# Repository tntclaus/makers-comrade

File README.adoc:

= Komrade of Maker (universal CNC platform)

[.right]
.First prototype, build volume (mm) 580x580x580
image::docs/img/photo_km-5.8.jpeg["First prototype",360]

This design is universal platform, that uses where available affordable parts, primarily from Reprap project, 8 bit realtime controllers, RPi 3/4 and Klipper.

Primary characteristics by application:

* 3D printing:
** Enclosed chamber passively heated up to 80ºC;
** Filament motion control;
** Auto bed levelling with Piezo Sensor and triple z axis;
** X/Y Linear speeds up to 200 mm/s (or greater with proper voltage/servos);
** Ceramic build surface.
* Milling with 585 series motors:
** Soft materials, e.g.: sheet plastics, plywood, aluminium (not tested);
** PCB prototyping.
* Laser cutting/engraving.
* Electrochemical machining.

== BOM
=== Base vitamins

.Base components common for all models
[cols="5,1,1,1",options="header",]
|===
|Part |Amount |Aliexpress |Amazon
|RAMPS 1.6+ |1 | - |-
|Arduino Mega |1 | - | -
|HDMI LCD 7" |1 | - | -
|RPi 3/4 |1 | - | -
|RPi Camera |1 | - | -
|RPi Motor Shield |1 | - | -
|Nema 17 steppers |5 | - | -
|X/Y axis MKS-Servo 42C |2 | - | -
|TMC 2209 |4 | - | -
|D16T parts set for universal X caret |1 | - | -
|V Slot Wheels|23 | - | -
|Steel parts for Z axis mount |1 | - | -
|Z axis axial bearing | 3 | - | -
|Z axis flexible coupler 5*8 |3 | - | -
|steel ball ø8mm |3 | - | -
|===

.Orbiter Extruder 3D Printer Toolhead
[cols="5,1,1,1",options="header",]
|===
|Part |Amount |Aliexpress |Amazon
|Extruder Orbiter with LDO stepper |1 | - | -
|Filament motion sensor |1 | - | -
|Crazy NF hotend | 1 | - | -
|===

=== Model KМ—3

Build Volume (mm): 300x300x300

[cols=",,,",options="header",]
|===
|Part |Amount |Aliexpress |Amazon
|  leadscrew  350 mm|  3  |  - | -
|  2020 VSlot extrusion 450 mm | 12 | - | -
|  2020 VSlot extrusion 850 mm | 4 | - | -
|  2040 VSlot extrusion 450 mm | 2 | - | -
|  GT6 Gates Belt (m) |  3  |  - | -
|===

=== Model KМ—6

Build Volume (mm): 600x600x600

== Dependencies

https://github.com/nophead/NopSCADlib
https://github.com/openscad/scad-utils
https://github.com/oysteinkrog/thing_libutils
https://github.com/Obijuan/obiscad

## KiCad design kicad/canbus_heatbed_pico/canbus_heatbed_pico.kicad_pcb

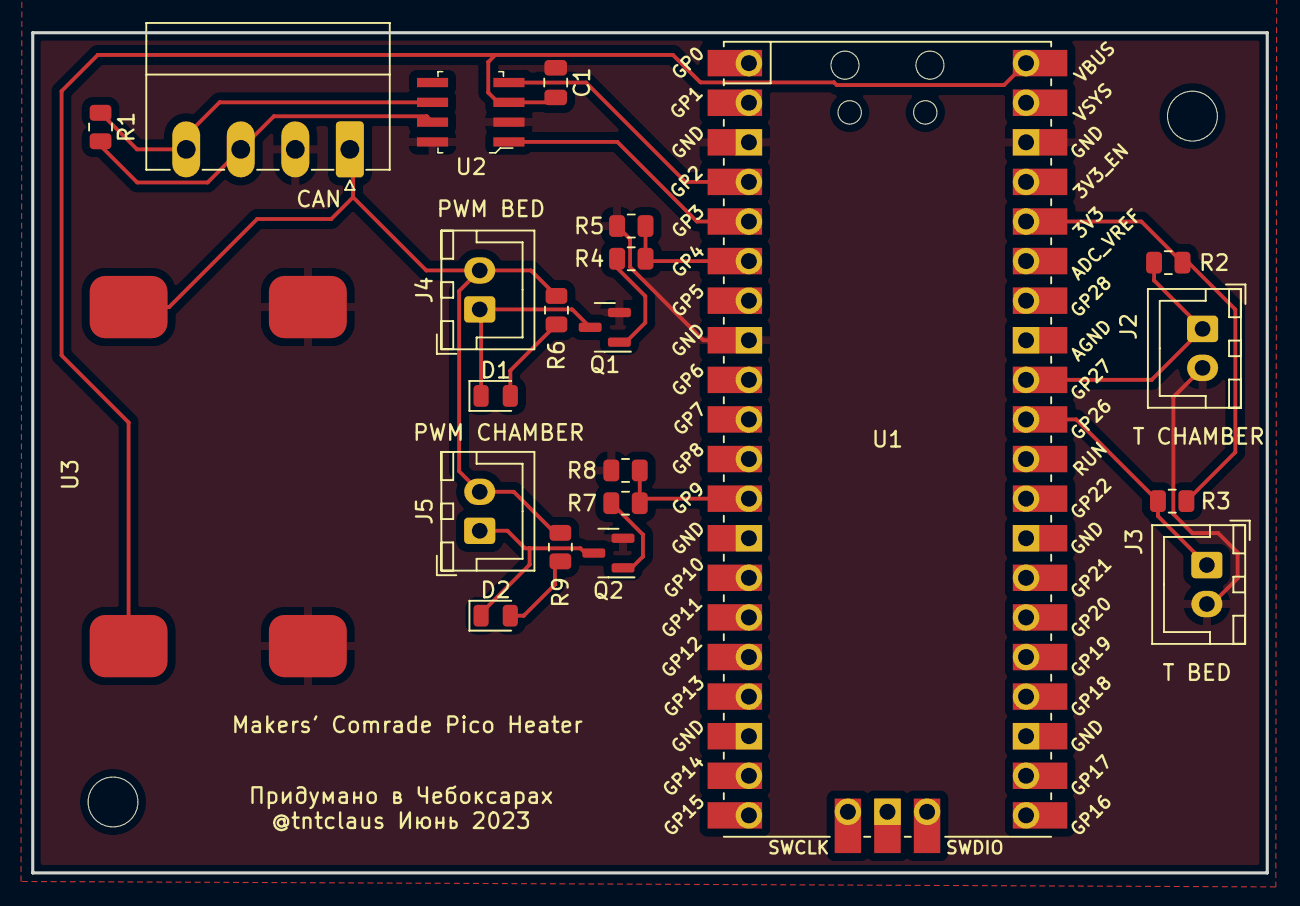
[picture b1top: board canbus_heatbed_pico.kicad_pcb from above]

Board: 2 copper layers, 79.2 x 53.9 mm, 24 parts (0 on the bottom side), 18 nets.

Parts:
C1: 0.1µF; C_0805_2012Metric
D1, D2: XL-2012UGC; LED_0805_2012Metric
H1, H2: MountingHole; MountingHole_3.2mm_M3_DIN965
J1: CAN; PhoenixContact_MC_1,5_4-G-3.5_1x04_P3.50mm_Horizontal
J2: T CHAMBER; JST_XH_B2B-XH-A_1x02_P2.50mm_Vertical
J3: T BED; JST_XH_B2B-XH-A_1x02_P2.50mm_Vertical
J4: PWM BED; JST_XH_B2B-XH-A_1x02_P2.50mm_Vertical
J5: PWM CHAMBER; JST_XH_B2B-XH-A_1x02_P2.50mm_Vertical
Q1, Q2: 2N7002K; SOT-23
R1: 120; R_0805_2012Metric
R2, R3, R5, R6, R8, R9: 4.7k; R_0805_2012Metric
R4, R7: 200; R_0805_2012Metric
U1: Pico; RPi_Pico_SMD_TH
U2: SN65HVD230DR; SOIC-8_W3.9mm
U3: MP1584EN 5V; MP1584EN

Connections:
+3V3: R2.1, R3.1, U1.36 (3V3)
+5V: C1.2, U1.40 (VBUS), U2.3 (VCC), U3.1 (5V)
+24V: J1.1, J4.2, J5.2, R6.2, R9.2, U3.3 (Vin+)
/CAN_RX: U1.4 (GPIO2), U2.4 (R)
/CAN_TX: U1.5 (GPIO3), U2.1 (D)
/H: J1.4, R1.1, U2.6 (CANL)
/L: J1.3, R1.2, U2.7 (CANH)
/PWM BED: R4.1, R5.1, U1.6 (GPIO4)
/PWM CHAMBER: R7.1, R8.1, U1.12 (GPIO9)
/T BED: J3.1, R3.2, U1.31 (GPIO26_ADC0)
/T CHAMBER: J2.1, R2.2, U1.32 (GPIO27_ADC1)
GND: C1.1, J1.2, J2.2, J3.2, Q1.2 (S), Q2.2 (S), R5.2, R8.2, U1.3 (GND), U1.8 (GND), U1.38 (GND), U2.2 (GND), U2.8 (RS), U3.2 (GND), U3.4 (Vin-)
unnamed: D1.1 (K), J4.1, Q1.3 (D)
unnamed: D1.2 (A), R6.1
unnamed: D2.1 (K), J5.1, Q2.3 (D)
unnamed: D2.2 (A), R9.1
unnamed: Q1.1 (G), R4.2
unnamed: Q2.1 (G), R7.2

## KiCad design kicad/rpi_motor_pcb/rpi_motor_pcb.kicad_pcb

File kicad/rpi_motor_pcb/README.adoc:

= Makers' Comrade CNC HAT

image::docs/pcb_3d.png[]

6-осевой ЧПУ шилд для Raspberry Pi 3B, 3B+, 4.

Возможности:

* Одновременное управление 6 драйверами шаговых двигателей:
** Поддерживаемые драйвера:
*** TMC2209, TMC2208 — режим UART с указанием адреса через перемычки MS1/MS2;
*** DRV8820, A4988 — обычный режим с конфигурацией через перемычки MS1,MS2,MS3;
* Любые другие драйвера, поддерживающие DIR/STEP.
* Суммарная пиковая производительность всех двигателей 1018 тыс. шагов/секунду (Klipper с патчем, Linux CNC не тестировался, но вероятно будет результат того же порядка).
* Поддержка концевиков для осей X, Y, Z, A, B, C как стандартного типа, так и DIAG выходов для без сенсорной парковки драйвера TMC2209.
* Поддержка дополнительного концевика (например, для датчика наличия/движения филамента 3д принтера).
* CANBUS host на базе MCP2515 и трансивера SN65HVD230:
** Даёт возможность гибкого дополнения станка периферией:
*** С контроллером экструдера https://github.com/makerbase-mks/MKS-THR36-THR42-UTC[MKS THR36] можно использовать как 3d принтер (не помешает canbus контроллер нагревательного стола/камеры).
*** С canbus контроллером шпинделя можно использовать как ЧПУ фрезер.
*** ...и т.д.
* Управление PWM нагрузкой с током до 1А (вентилятор обдува, маломощный двигатель).
* Поддерживаемые системы: Linux CNC, Klipper.

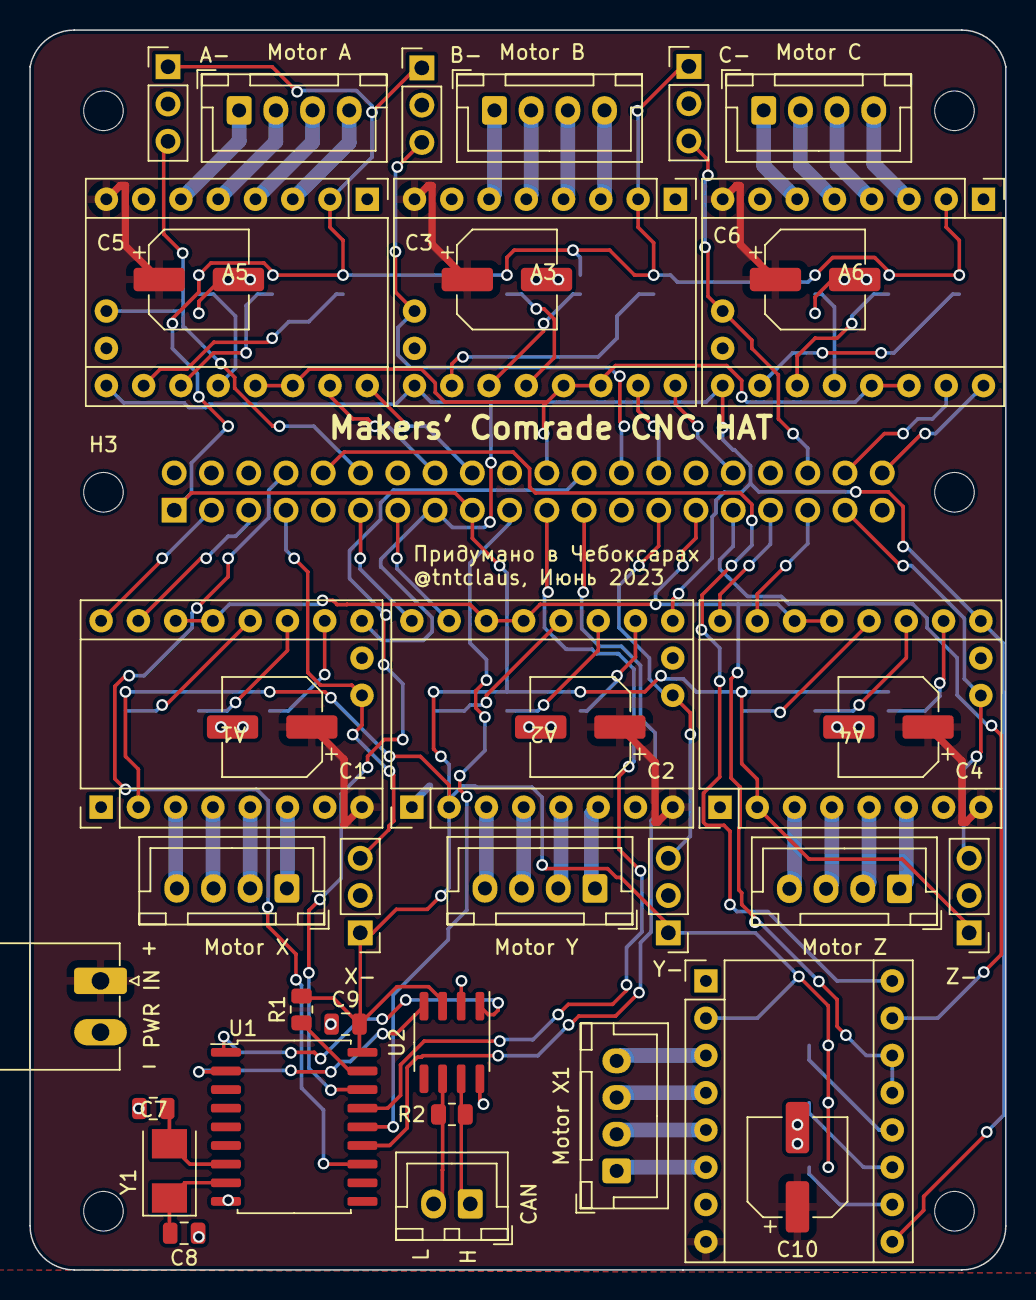
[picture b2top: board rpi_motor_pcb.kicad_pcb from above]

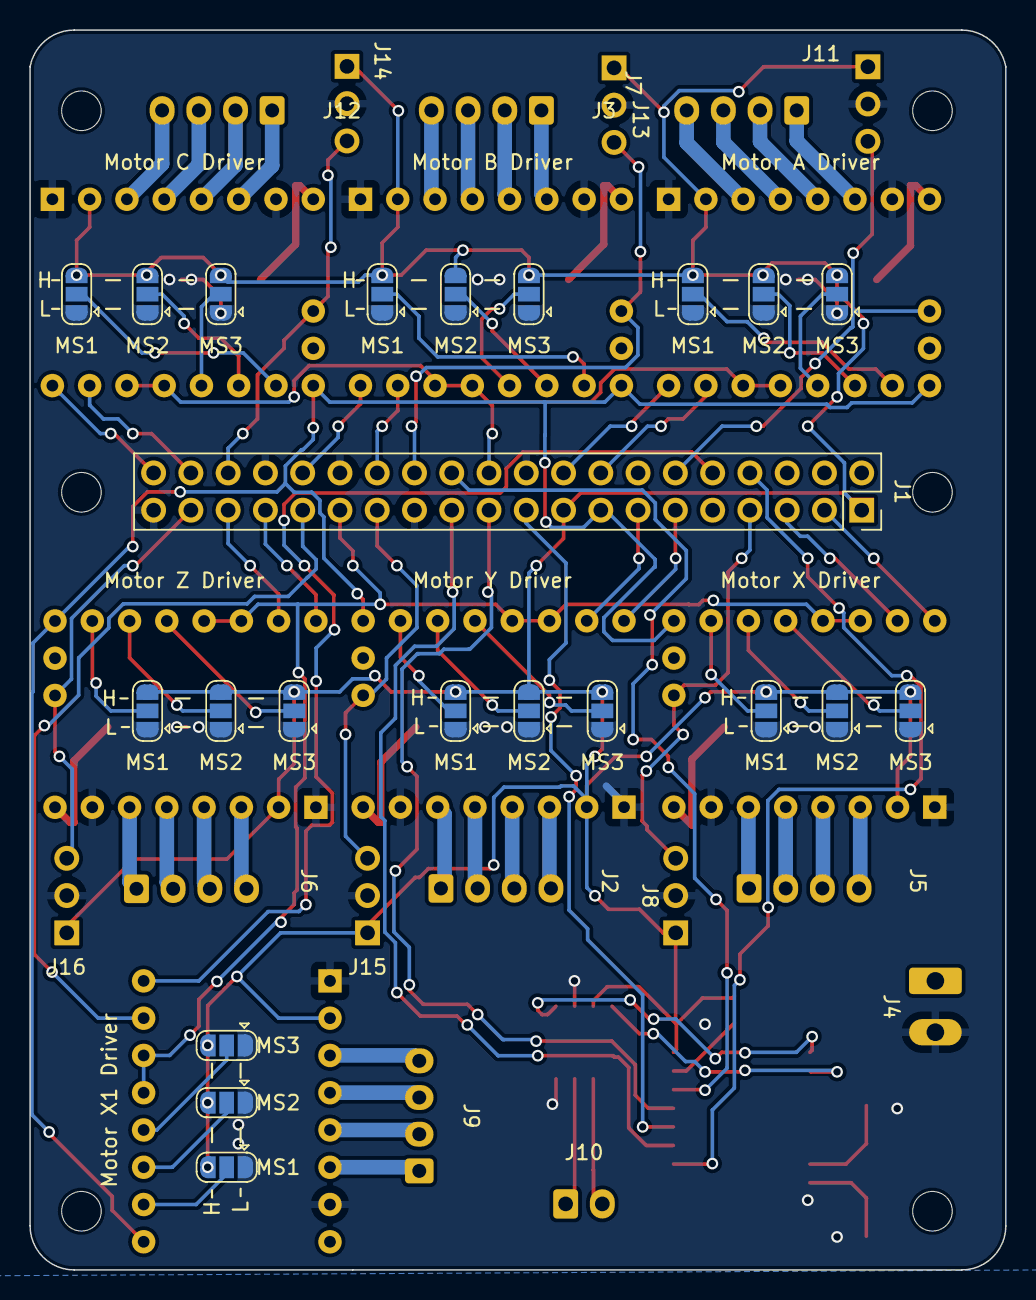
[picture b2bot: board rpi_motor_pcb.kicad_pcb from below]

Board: 2 copper layers, 66.5 x 84.5 mm, 65 parts (22 on the bottom side), 87 nets.

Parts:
A1: Motor X Driver; TMC220X
A2: Motor Y Driver; TMC220X
A3: Motor B Driver; TMC220X
A4: Motor Z Driver; TMC220X
A5: Motor A Driver; TMC220X
A6: Motor C Driver; TMC220X
A7: Motor X1 Driver; TMC2208
C1, C2, C3, C4, C5, C6, C10: 100µF 50V; CP_Elec_6.3x7.7
C7, C8: 22pF; C_0805_2012Metric
C9: 0.1µF; C_0805_2012Metric
H1, H2, H3, H4, H5, H6: MountingHole; MountingHole_2.7mm_M2.5_ISO14580
J1: Raspberry_Pi_2_3; PinSocket_2x20_P2.54mm_Vertical
J2: Motor Y; JST_XH_B4B-XH-A_1x04_P2.50mm_Vertical
J3: Motor B; JST_XH_B4B-XH-A_1x04_P2.50mm_Vertical
J4: PWR IN; PhoenixContact_MC_1,5_2-G-3.5_1x02_P3.50mm_Horizontal
J5: Motor X; JST_XH_B4B-XH-A_1x04_P2.50mm_Vertical
J6: Motor Z; JST_XH_B4B-XH-A_1x04_P2.50mm_Vertical
J7: Motor A; JST_XH_B4B-XH-A_1x04_P2.50mm_Vertical
J8: X-; PinHeader_1x03_P2.54mm_Vertical
J9: Motor X1; JST_XH_B4B-XH-A_1x04_P2.50mm_Vertical
J10: CAN; JST_XH_B2B-XH-A_1x02_P2.50mm_Vertical
J11: A-; PinHeader_1x03_P2.54mm_Vertical
J12: Motor C; JST_XH_B4B-XH-A_1x04_P2.50mm_Vertical
J13: B-; PinHeader_1x03_P2.54mm_Vertical
J14: C-; PinHeader_1x03_P2.54mm_Vertical
J15: Y-; PinHeader_1x03_P2.54mm_Vertical
J16: Z-; PinHeader_1x03_P2.54mm_Vertical
JP1, JP4, JP7, JP10, JP13, JP16, JP19: MS3; SolderJumper-3_P1.3mm_Open_RoundedPad1.0x1.5mm
JP2, JP5, JP8, JP11, JP14, JP17, JP20: MS2; SolderJumper-3_P1.3mm_Open_RoundedPad1.0x1.5mm
JP3, JP6, JP9, JP12, JP15, JP18, JP21: MS1; SolderJumper-3_P1.3mm_Open_RoundedPad1.0x1.5mm
R1: 10k; R_0805_2012Metric
R2: 120; R_0805_2012Metric
U1: MCP2515-xSO; SOIC-18W_7.5x11.6mm_P1.27mm
U2: SN65HVD230; SOIC-8_3.9x4.9mm_P1.27mm
Y1: Crystal; Crystal_SMD_5032-2Pin_5.0x3.2mm

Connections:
+3V3: A1.2 (VDD), A2.2 (VDD), A3.2 (VDD), A4.2 (VDD), A5.2 (VDD), A6.2 (VDD), A7.2 (VDD), C9.2, J1.1 (3V3), J1.17 (3V3), J8.1, J11.1, J13.1, J14.1, J15.1, J16.1, JP1.3 (B), JP2.3 (B), JP3.3 (B), JP4.3 (B), JP5.3 (B), JP6.3 (B), JP7.3 (B), JP8.3 (B), JP9.3 (B), JP10.3 (B), JP11.3 (B), JP12.3 (B), JP13.3 (B), JP14.3 (B), JP15.3 (B), JP16.3 (B), JP17.3 (B), JP18.3 (B), JP19.3 (B), JP20.3 (B), JP21.3 (B), R1.2, U1.18 (VDD), U2.3 (VCC)
/CAN/H: J10.1, R2.1, U2.7 (CANH)
/CAN/L: J10.2, R2.2, U2.6 (CANL)
/CAN/RX: U1.2 (RXCAN), U2.4 (R)
/CAN/TX: U1.1 (TXCAN), U2.1 (D)
/CAN_CS: J1.24 (~CE0/GPIO8), U1.16 (~CS)
/CAN_INT: J1.8 (GPIO14/TXD), U1.12 (~INT)
/CAN_MISO: J1.21 (MISO0/GPIO9), U1.15 (SO)
/CAN_MOSI: J1.19 (MOSI0/GPIO10), U1.14 (SI)
/CAN_SCK: J1.23 (SCLK0/GPIO11), U1.13 (SCK)
/MA DIAG: A5.18 (DIAG), J1.12 (GPIO18/PWM0), J11.3
/MA DIR: A5.16 (DIR), J1.18 (GPIO24)
/MA STEP: A5.15 (STEP), J1.16 (GPIO23)
/MB DIAG: A3.18 (DIAG), J1.26 (~CE1/GPIO7), J13.3
/MB DIR: A3.16 (DIR), J1.32 (PWM0/GPIO12)
/MB STEP: A3.15 (STEP), J1.28 (ID_SC/GPIO1)
/MC DIAG: A6.18 (DIAG), J1.36 (GPIO16), J14.3
/MC DIR: A6.16 (DIR), J1.40 (GPIO21/SCLK1)
/MC STEP: A6.15 (STEP), J1.38 (GPIO20/MOSI1)
/MX1 DIR: A7.16 (DIR), J1.10 (GPIO15/RXD)
/MX1 STEP: A7.15 (STEP), J1.31 (GCLK2/GPIO6)
/MX DIAG: A1.18 (DIAG), J1.7 (GCLK0/GPIO4), J8.3
/MX DIR: A1.16 (DIR), J1.3 (SDA/GPIO2)
/MX STEP: A1.15 (STEP), J1.5 (SCL/GPIO3)
/MY DIAG: A2.18 (DIAG), J1.27 (ID_SD/GPIO0), J15.3
/MY DIR: A2.16 (DIR), J1.11 (GPIO17)
/MY STEP: A2.15 (STEP), J1.13 (GPIO27)
/MZ DIAG: A4.18 (DIAG), J1.37 (GPIO26), J16.3
/MZ DIR: A4.16 (DIR), J1.33 (PWM1/GPIO13)
/MZ STEP: A4.15 (STEP), J1.35 (GPIO19/MISO1)
/Motor A/1A: A5.4 (1A), J7.3
/Motor A/1B: A5.3 (1B), J7.4
/Motor A/2A: A5.5 (2A), J7.2
/Motor A/2B: A5.6 (2B), J7.1
/Motor A/MS1: A5.10 (MS1), JP15.2 (C)
/Motor A/MS2: A5.11 (MS2), JP14.2 (C)
/Motor A/MS3: A5.12 (NC/TX), JP13.2 (C)
/Motor B/1A: A3.4 (1A), J3.3
/Motor B/1B: A3.3 (1B), J3.4
/Motor B/2A: A3.5 (2A), J3.2
/Motor B/2B: A3.6 (2B), J3.1
/Motor B/MS1: A3.10 (MS1), JP9.2 (C)
/Motor B/MS2: A3.11 (MS2), JP8.2 (C)
/Motor B/MS3: A3.12 (NC/TX), JP7.2 (C)
/Motor C/1A: A6.4 (1A), J12.3
/Motor C/1B: A6.3 (1B), J12.4
/Motor C/2A: A6.5 (2A), J12.2
/Motor C/2B: A6.6 (2B), J12.1
/Motor C/MS1: A6.10 (MS1), JP18.2 (C)
/Motor C/MS2: A6.11 (MS2), JP17.2 (C)
/Motor C/MS3: A6.12 (NC/TX), JP16.2 (C)
/Motor X1/1A: A7.4 (1A), J9.3
/Motor X1/1B: A7.3 (1B), J9.4
/Motor X1/2A: A7.5 (2A), J9.2
/Motor X1/2B: A7.6 (2B), J9.1
/Motor X1/MS1: A7.10 (MS1), JP21.2 (C)
/Motor X1/MS2: A7.11 (MS2), JP20.2 (C)
/Motor X1/MS3: A7.12 (NC/TX), JP19.2 (C)
/Motor X/1A: A1.4 (1A), J5.3
/Motor X/1B: A1.3 (1B), J5.4
/Motor X/2A: A1.5 (2A), J5.2
/Motor X/2B: A1.6 (2B), J5.1
/Motor X/MS1: A1.10 (MS1), JP3.2 (C)
/Motor X/MS2: A1.11 (MS2), JP2.2 (C)
/Motor X/MS3: A1.12 (NC/TX), JP1.2 (C)
/Motor Y/1A: A2.4 (1A), J2.3
/Motor Y/1B: A2.3 (1B), J2.4
/Motor Y/2A: A2.5 (2A), J2.2
/Motor Y/2B: A2.6 (2B), J2.1
/Motor Y/MS1: A2.10 (MS1), JP6.2 (C)
/Motor Y/MS2: A2.11 (MS2), JP5.2 (C)
/Motor Y/MS3: A2.12 (NC/TX), JP4.2 (C)
/Motor Z/1A: A4.4 (1A), J6.3
/Motor Z/1B: A4.3 (1B), J6.4
/Motor Z/2A: A4.5 (2A), J6.2
/Motor Z/2B: A4.6 (2B), J6.1
/Motor Z/MS1: A4.10 (MS1), JP12.2 (C)
/Motor Z/MS2: A4.11 (MS2), JP11.2 (C)
/Motor Z/MS3: A4.12 (NC/TX), JP10.2 (C)
/UART_A: A3.13 (PDN/RX), A3.14 (NC/CLK), A5.13 (PDN/RX), A5.14 (NC/CLK), A6.13 (PDN/RX), A6.14 (NC/CLK), J1.22 (GPIO25)
/UART_X: A1.13 (PDN/RX), A1.14 (NC/CLK), A2.13 (PDN/RX), A2.14 (NC/CLK), A4.13 (PDN/RX), A4.14 (NC/CLK), A7.13 (PDN/RX), A7.14 (NC/CLK), J1.29 (GCLK1/GPIO5)
GND: A1.1 (GND), A1.7 (GND), A2.1 (GND), A2.7 (GND), A3.1 (GND), A3.7 (GND), A4.1 (GND), A4.7 (GND), A5.1 (GND), A5.7 (GND), A6.1 (GND), A6.7 (GND), A7.1 (GND), A7.7 (GND), C1.2, C2.2, C3.2, C4.2, C5.2, C6.2, C7.1, C8.1, C9.1, C10.2, J1.20 (GND), J1.25 (GND), J1.30 (GND), J1.34 (GND), J1.39 (GND), J4.2, J8.2, J11.2, J13.2, J14.2, J15.2, J16.2, JP1.1 (A), JP2.1 (A), JP3.1 (A), JP4.1 (A), JP5.1 (A), JP6.1 (A), JP7.1 (A), JP8.1 (A), JP9.1 (A), JP10.1 (A), JP11.1 (A), JP12.1 (A), JP13.1 (A), JP14.1 (A), JP15.1 (A), JP16.1 (A), JP17.1 (A), JP18.1 (A), JP19.1 (A), JP20.1 (A), JP21.1 (A), U1.9 (VSS), U2.2 (GND), U2.8 (Rs)
MEN: A1.9 (~ENABLE), A2.9 (~ENABLE), A3.9 (~ENABLE), A4.9 (~ENABLE), A5.9 (~ENABLE), A6.9 (~ENABLE), A7.9 (~ENABLE), J1.15 (GPIO22)
unnamed: C7.2, U1.7 (OSC2), Y1.2
unnamed: C8.2, U1.8 (OSC1), Y1.1
unnamed: R1.1, U1.17 (~RESET)
Vin: A1.8 (VMOT), A2.8 (VMOT), A3.8 (VMOT), A4.8 (VMOT), A5.8 (VMOT), A6.8 (VMOT), A7.8 (VMOT), C1.1, C2.1, C3.1, C4.1, C5.1, C6.1, C10.1, J4.1

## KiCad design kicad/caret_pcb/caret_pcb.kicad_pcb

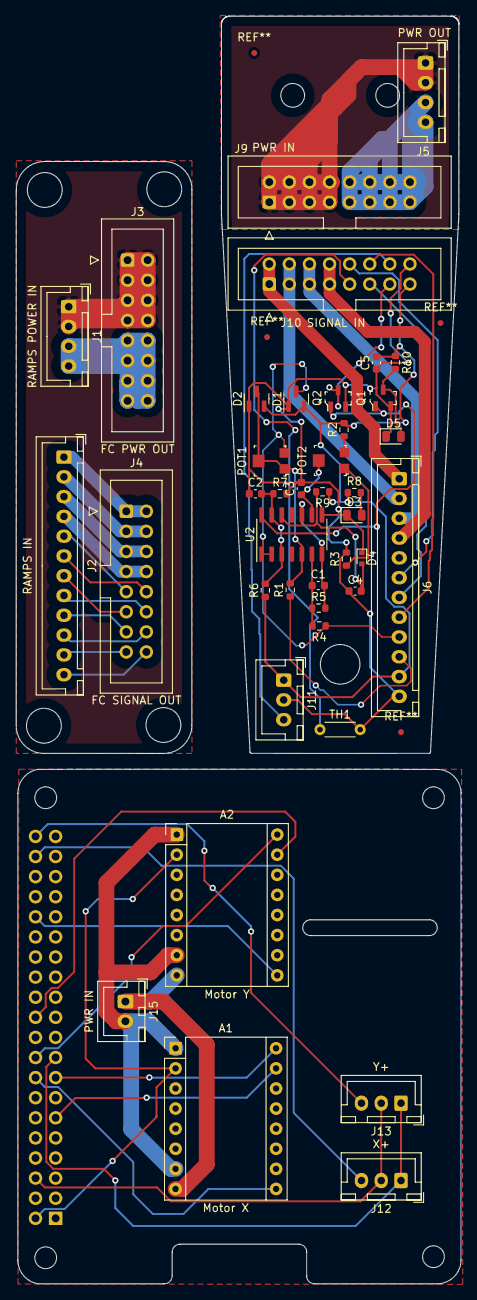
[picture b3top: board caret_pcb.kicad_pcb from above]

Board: 2 copper layers, 56.2 x 160.2 mm, 41 parts (1 on the bottom side), 55 nets.

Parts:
A1: Motor X; Pololu_Breakout-16_15.2x20.3mm
A2: Motor Y; Pololu_Breakout-16_15.2x20.3mm
C1, C2, C3: 0.1uF; C_0603_1608Metric
C4, C5: 1 uF 10 V 10%; C_0603_1608Metric
D1, D2: BAV99; SOT-23
D3: RED; D_0805_2012Metric
D4: RB751S40T1G; D_SOD-523
D5: BLUE; D_0805_2012Metric
J1: RAMPS POWER IN; JST_XH_B4B-XH-A_1x04_P2.50mm_Vertical
J2: RAMPS IN; JST_XH_B12B-XH-A_1x12_P2.50mm_Vertical
J3: FC PWR OUT; IDC-Header_2x08_P2.54mm_Vertical
J4: FC SIGNAL OUT; IDC-Header_2x08_P2.54mm_Vertical
J5: PWR OUT; JST_XH_B4B-XH-A_1x04_P2.50mm_Vertical
J6: TOOLHEAD; JST_XH_B12B-XH-A_1x12_P2.50mm_Vertical
J9: PWR IN; IDC-Header_2x08_P2.54mm_Vertical
J10: SIGNAL IN; IDC-Header_2x08_P2.54mm_Vertical
J11: Endstop Y; JST_XH_B3B-XH-A_1x03_P2.50mm_Vertical
J12: X+; JST_XH_B3B-XH-A_1x03_P2.50mm_Vertical
J13: Y+; JST_XH_B3B-XH-A_1x03_P2.50mm_Vertical
J14: Raspberry_Pi_2_3; PinSocket_2x20_P2.54mm_Vertical
J15: PWR IN; JST_XH_B2B-XH-A_1x02_P2.50mm_Vertical
POT1: TC33X-2-105; Trimpot_3.8mmx3.6mm_TC33X-2-103E
POT2: TC33X-2-104; Trimpot_3.8mmx3.6mm_TC33X-2-103E
Q1, Q2: BSS138BK; SOT-23-3
R1, R6, R7: 10k; R_0603_1608Metric
R2: 330k; R_0603_1608Metric
R3: 390k; R_0603_1608Metric
R4: 20k; R_0603_1608Metric
R5: 82k; R_0603_1608Metric
R8: 510; R_0603_1608Metric
R9: 1M; R_0603_1608Metric
R10: 1k; R_0603_1608Metric
TH1: Thermistor_NTC; R_Axial_DIN0204_L3.6mm_D1.6mm_P5.08mm_Horizontal
U2: LM324; SOIC-14_3.9x8.7mm_P1.27mm

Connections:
/Caret Adapter/1A: J6.2, J10.3, J10.4
/Caret Adapter/1B: J6.1, J10.1, J10.2
/Caret Adapter/2A: J6.3, J10.5, J10.6
/Caret Adapter/2B: J6.4, J10.7, J10.8
/Caret Adapter/5V+: C5.2, D1.2 (A), D2.2 (A), J6.11, J10.15, J11.1, R2.2, R6.1, R8.1, R9.1, R10.1
/Caret Adapter/End.Y: J10.14, J11.3
/Caret Adapter/GND: C2.1, C3.2, C4.1, C5.1, D1.1 (K), D2.1 (K), D5.1 (K), J6.12, J10.16, J11.2, Q1.2 (S), Q2.2 (S), R3.2, R7.2, TH1.2
/Caret Adapter/HE0+: J5.1, J5.2, J9.1, J9.2, J9.3, J9.4, J9.5, J9.6, J9.7, J9.8
/Caret Adapter/PWM 5V: J6.8, J10.12
/Caret Adapter/PZ+: D1.3 (K), J6.9, POT1.3 (CW), R4.1, U2.1, U2.2 (-)
/Caret Adapter/PZ-: J6.10, R1.1
/Caret Adapter/T.enc: J10.9, TH1.1
/Caret Adapter/T.ext: J6.6, J10.10
/Caret Adapter/T.hbr: J6.7, J10.11
/Caret Adapter/Z+: J10.13, Q2.3 (D)
/RAMPS Adapter/+5V: J2.11, J4.15
/RAMPS Adapter/A3/T.hbr: J2.7, J4.11
/RAMPS Adapter/A4/T.ext: J2.6, J4.10
/RAMPS Adapter/A13/T.enc: J2.5, J4.9
/RAMPS Adapter/D6/PWM 5V: J2.8, J4.12
/RAMPS Adapter/D39/End.Y: J2.10, J4.14
/RAMPS Adapter/D45/End.Z: J2.9, J4.13
/RAMPS Adapter/E0 1A: J2.2, J4.3, J4.4
/RAMPS Adapter/E0 1B: J2.1, J4.1, J4.2
/RAMPS Adapter/E0 2A: J2.3, J4.5, J4.6
/RAMPS Adapter/E0 2B: J2.4, J4.7, J4.8
/RAMPS Adapter/GND_RAMPS: J2.12, J4.16
/RAMPS Adapter/HE0+: J1.1, J1.2, J3.1, J3.2, J3.3, J3.4, J3.5, J3.6, J3.7, J3.8
/RPi Motor/GNDmot: A1.1 (GND), A1.7 (GND), A2.1 (GND), A2.7 (GND), J15.2
/RPi Motor/MotX DIR: A1.16 (DIR), J14.15 (GPIO22)
/RPi Motor/MotX En: A1.9 (~ENABLE), J14.16 (GPIO23)
/RPi Motor/MotX Step: A1.15 (STEP), J14.11 (GPIO17)
/RPi Motor/MotY DIR: A2.16 (DIR), J14.18 (GPIO24)
/RPi Motor/MotY En: A2.9 (~ENABLE), J14.32 (PWM0/GPIO12)
/RPi Motor/MotY Step: A2.15 (STEP), J14.22 (GPIO25)
/RPi Motor/Vmot: A1.8 (VMOT), A2.8 (VMOT), J15.1
/RPi Motor/X+: J12.3, J14.38 (GPIO20/MOSI1)
/RPi Motor/Y+: J13.3, J14.40 (GPIO21/SCLK1)
GND1: J5.3, J5.4, J9.9, J9.10, J9.11, J9.12, J9.13, J9.14, J9.15, J9.16
GNDREF: J1.3, J1.4, J3.9, J3.10, J3.11, J3.12, J3.13, J3.14, J3.15, J3.16
unnamed: A1.2 (VDD), A2.2 (VDD), J14.4 (5V)
unnamed: C1.1, R4.2, R5.1, U2.6 (-)
unnamed: C1.2, R5.2, U2.7, U2.10 (+)
unnamed: C2.2, R6.2, R7.1, U2.3 (+), U2.13 (-)
unnamed: C3.1, POT2.2 (Wiper), U2.9 (-)
unnamed: C4.2, D4.2 (A), R9.2, U2.12 (+)
unnamed: D2.3 (K), POT1.1 (CCW), POT1.2 (Wiper), R1.2, U2.5 (+)
unnamed: D3.1 (K), D4.1 (K), U2.8
unnamed: D3.2 (A), R8.2
unnamed: D5.2 (A), Q1.3 (D), R10.2
unnamed: J12.1, J13.1, J14.17 (3V3)
unnamed: J12.2, J13.2, J14.6 (GND)
unnamed: POT2.1 (CCW), R3.1
unnamed: POT2.3 (CW), R2.1
unnamed: Q1.1 (G), Q2.1 (G), U2.14

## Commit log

2020-06-26 y axis done
2020-07-26 case done
2020-08-02 changed gantries and added dxfs
2020-11-01 rev 1: почти всё есть кроме корпуса + недоделанный fan duct
2020-11-01 - svgs
2020-11-02 fix x axis mirror and duct render
2020-11-03 fun duct model
2020-11-04 fixes to fun duct
2020-11-04 funduct stl + blower vitamin
2020-11-04 cable chain holder
2020-11-15 added titan extruder model
2021-01-26 double rail printhead work
2021-01-26 readme and other
2021-03-09 версия с 2 рельсами
2021-03-11 spindle lib
2021-03-11 spindle lib split
2021-03-11 spindle vitamins
2021-03-16 голова шпинделя, в целом готвая каретка X
2021-03-18 extruder toolhead and caret belt lock part
2021-03-20 fix mount holes on X caret
2021-03-21 added v6 collet lock to extruder toolhead
2021-03-28 added v6 ptfe collet
2021-03-28 comment out echos
2021-03-30 v6 radiator cooler
2021-04-14 extruder complete
2021-04-26 new heat bed wip; refactor toolhead utils; new spindle toohead plates and piezo
2021-04-26 fix assymbly preview
2021-04-26 z-axis gantry wip
2021-05-07 new z axis and heatbed
2021-05-07 spool holder
2021-05-07 klipper config
2021-05-08 fix spool rod nuts
2021-05-08 z gantry holder should have mounts for PC part
2021-05-08 added spherical nuts
2021-05-08 added spherical nuts: remove test render
2021-05-08 z_gantry bed minirails
2021-05-08 z_gantry mini rail mount hole for tapping
2021-05-09 z_gantry fix lead screw mounts
2021-05-16 thrust bearing
2021-05-16 thrust bearing support for z axis
2021-05-16 correct stl for spindle collet
2021-05-16 dxf path length calculation script
2021-05-30 z axis top pillow block
2021-05-30 support 2d triangle
2021-05-30 improve tube adapter
2021-05-30 fix wheels distance; y caret now has 4 wheels and centered belts
2021-05-30 rename extruder toolhead
2021-06-20 toolhead_extruder: add orbiter, upgrade e3d heatberak cooler mount, refactoring
2021-11-08 lib: add mosquito radiator + makers_comrade_hotend prototype
2021-11-08 lib: refactor e3d nozzle — moved to dedicated scad file + v6 nozzle stl
2021-11-08 hotend_mosquito: fix rotation and add dimension functions
2021-11-08 hotend_mosquito: add mosquito magnum hotend
2021-11-08 utils: add tube from shape module
2021-11-08 fan_duct: add splitter for double hose nozzle cooling
2021-11-08 toolhead_extruder: refactoring
2021-11-08 toolhead_extruder: added mosquito cooler case wip
2021-11-27 readme: added bom
2021-11-27 refactor adoc
2021-11-27 removed stale stl files
2021-11-27 extruder/hotend refactoring
2021-11-27 toolheads: mosquito small fixes
2021-11-27 toolheads: fixed spindle toolhead errors
2021-11-27 x-axis: fixed errors after gantry refactoring
2021-11-27 x-axis: encapsulate working space and safe margins calculation
2021-11-27 y-axis: encapsulate working space and safe margins calculation
2021-11-28 z-axis: encapsulate working space and safe margins calculation
2021-11-28 ignore bom
2021-11-28 3d_printer: add main assembly
2021-11-29 3d_printer: add x/y motor plates and corner belt pulley plates
2021-11-29 dxf_length_calc: calculate total length of dxf cuts and approxiamte price for laser cutting of steel and d16
2021-11-29 heatbed: fix vitamin name
2021-11-29 frame: add belt corner pulleys assembly with 3d printed spacers
2021-11-29 3d_printer: corexy belt and pulleys
2021-11-29 z-axis: correct height
2021-11-29 y-axis: fix caret positioning
2021-11-29 heatbed: support rectangular shape
2021-11-29 enclosure: front and rear case parts
2021-11-30 enclosure: all parts except bottom
2021-11-30 refactoring
2021-12-01 enclosure: almost done all parts + refactoring
2021-12-01 x-axis: improve performance with pure 2d shapes
2021-12-03 enclosure: top door
2021-12-05 z-axis: add anti-wobble rings
2021-12-05 z-axis: remove global constant
2021-12-22 enclosure: z-axis mounts + reworked side windows
2021-12-22 enclosure: x/y motor windows
2022-01-15 heat_bed_heater: support different material types
2022-03-06 everything: lots of changes
2022-03-07 enclosure: top part corner extrusions
2022-03-08 enclosure: polycarbonate parts done
2022-03-13 multiple: six stl exports
2022-03-13 enclosure: fix gaslift mount
2022-03-21 motor plates: change screw to be screwed from top
2022-03-21 axes: cosmetics
2022-03-21 gas_spring: added
2022-03-21 leadscrew_anti_z_wobble: in nut mount part fixed leadscrew hole, fixed mount cylinders height
2022-03-21 enclosure_sides: motors side — swapped elevation of x/y motors and, motor plate windows now count coloring thickness
2022-03-21 enclosure_front: hinge now has 3 mounts
2022-03-21 enclosure_back: hinge now has 3 mounts, fixed misplaced hinge mounts on enclosure
2022-03-21 enclosure_front: fix magnet positioning at front doors and add magnets to bom
2022-03-21 enclosure_door_top: added handle
2022-03-21 enclosure_door_top: offset metal parts from edge
2022-03-21 enclosure_door_top: hide test
2022-03-22 z-axis: fix z ganry table mount block
2022-03-22 enclosure_doors: front door handle
2022-03-22 x-axis: opto endstop mount
2022-03-23 cable_chain: section
2022-03-25 enclosure_doors: door handle stl
2022-03-25 cable_chain: chain segment
2022-03-25 enclosure_doors: remove test
2022-03-28 enclosure_doors_top: comment out test
2022-03-28 toolhead_extruder_orbiter: fix some issues
2022-03-28 toolhead_extruder_orbiter: comment out test
2022-03-28 electronics_box.scad: fixed case vesa mount, added sensor cover mount
2022-03-28 cable_chain.scad: added blower and filament tubes mounts
2022-03-30 cable_chain.scad: added cable chain caret mount
2022-03-31 cable_chain.scad: all cable chain parts designed
2022-04-02 toolhead_laser_lasertree_80w: add lasertree laser cutter toolhead
2022-04-03 electronics_box.scad: added filament sensor mount
2022-04-04 electronics_box.scad: fix screws
2022-04-22 pcb designs
2022-04-22 klipper_config: add sample configs
2022-05-06 kicad.caret_pcb: add 3d printer boards
2022-07-06 toolhead_extruder_heatbreak_mosquito_cooler.scad: moved piezo disc location to bottom for better sensitivity
2022-07-06 toolhead_extruder_heatbreak_mosquito_cooler.scad: fix cooling part
2022-07-06 toolhead_extruder_heatbreak_mosquito_cooler.scad: fixed wire mounts and moved piezo disk to new location
2022-07-07 toolhead_extruder_heatbreak_mosquito_cooler.scad: improve middle part
2022-07-07 caret_cable_chain: size fixes
2022-07-07 caret_pcb: fix power line
2022-07-07 electronics_box: added mains inlet
2022-07-07 heatbed: changed example
2022-07-07 hotend_mc: custom high performance hotend
2022-07-07 mk8_hotend: move to lib
2022-07-07 gitignore: kicad support
2022-07-08 enclusure side dual z: added cable_chain_enclousure_outer_mount
2022-08-06 heatbeds: refactor and add concrete heatbed molds
2022-10-08 main_cnc_router: first version
2022-10-15 cnc_router: metal parts done
2022-10-15 caret_pcb: fix piezo sensor power line, fix rpi shield schematic
2022-11-11 cnc_router: dxf fixes
2022-11-11 caret_cable_chain: commit
2022-11-11 enclosures: split to have full/light enclosure.
2022-11-11 toolhead_extruder_heatbreak_mosquito: fix stl namings
2022-11-24 refactor enclosure types
2022-11-25 toolhead.spindles: refactor and add rs385 motor
2022-11-29 toolhead_spindle_generic_plastic: fix latch height
2022-12-23 vwheel: improve vwheel lib consistency
2022-12-23 main_cnc_router: fix z gantry
2023-01-07 y_axis: added pulley cap
2023-01-23 cnc_router: added gears
2023-01-24 cyclone_dust_collector: init
2023-01-25 remove old stls
2023-01-25 heatbeds: refactoring, moved to common tool tables package common for work surfaces
2023-01-31 move cyclone to lib
2023-01-31 refactor tooltables
2023-05-29 рабочая плата rpi motor
2023-06-01 rpi_motor_pcb: 6-axis canbus version
2023-06-01 rpi_motor_pcb: fix README.adoc
2023-06-01 rpi_motor_pcb: a,b,c endstops
2023-06-02 lib: moved cable_chain to separate repository
2023-06-04 rpi_motor_pcb: 6-axis fix diag pin, add en pin
2023-06-04 rpi_motor_pcb: 7-axis canbus version (removed useless fan and limit switch)
2023-06-04 rpi_motor_pcb: fix ms hints
2023-07-11 rpi_motor_pcb: 6 axis version
2023-07-15 heater_pcb: kicad generator
2023-07-16 lib: external libs
2023-07-16 heater_pcb: fix errors
2023-07-24 heater_pcb: added real track resistance at 20 and 100ºC
2023-12-31 lib: refactor cable chain dependency
2023-12-31 lib: complete migration to vslot_wheels and cable shain library
2023-12-31 прижимной ролик для х/у
2023-12-31 lib: tiny belt tensioner
2023-12-31 fix import errors
2024-01-03 kicad: heatber pico controller prototype
2024-02-27 fix enclosure refactoring warnings
2024-02-28 caret_pcb: fix import
2024-03-01 lib/cable_chain: update dependency
